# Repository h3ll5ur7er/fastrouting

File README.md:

# traxide

*trace* + *oxide*: a fast, dependency-free PCB autorouter for KiCad and every tool that speaks Specctra DSN: a modern alternative to Freerouting, written in Rust, using every CPU core and, when present, the GPU.

> traxide is young: it routes a 4-layer keyboard with an RP2350 completely in seconds, and KiCad 10's DRC finds the result clean, while Freerouting takes minutes and leaves violations. It reads KiCad's board files and Specctra DSN, and has met few boards yet. See the [benchmarks](docs/Benchmarks.md).

## Try it

Download traxide and its KiCad plugin from the repository's **Releases**: archives for Linux, Windows (x86-64 and ARM64 each) and macOS (universal), with nothing else to install, and a KiCad package for each. Between releases, every push builds the same in the **Binaries** workflow under the *Actions* tab. Or build it:

```bash
cargo build --release
# A KiCad 9 or 10 board, with the rules of its project: writes board.routed.kicad_pcb
target/release/traxide route board.kicad_pcb
# Or, as with Freerouting: in KiCad, File → Export → Specctra DSN, then
target/release/traxide route board.dsn        # writes board.ses, on all cores
target/release/traxide route --help           # profiles, threads, output
target/release/traxide route board.dsn --time-limit 60   # stop negotiating after a minute
target/release/traxide check board.dsn board.ses   # complete? rules broken?
# The same verdict as a DRC report in KiCad's JSON format (route takes --drc too)
target/release/traxide check board.dsn board.ses --drc board.drc.json
# In place of Freerouting: the same arguments, -drc report.json included
target/release/traxide freerouting -de board.dsn -do board.ses
# In KiCad: File → Import → Specctra Session
```

### From inside KiCad

traxide's KiCad plugin adds a **Route board** button to the PCB editor's toolbar (KiCad 9 and 10). It routes every unrouted connection of the open board and adds the routes as one step: *Edit → Undo traxide: route* takes them all back. The rules come from KiCad's net classes and the project's files. On a board with copper zones traxide then refills them around the routes, a step of its own, so taking the routes back takes two undos.

1. **Enable KiCad's API first**: *Preferences → Preferences… → Plugins → Enable KiCad API*. It is off by default, and **without it KiCad shows no traxide button at all**.
2. Download the KiCad package for your platform (`traxide-kicad-<version>-<platform>.zip`) from the Releases and install it with *Plugin and Content Manager → Install from File…*.
3. Restart the PCB editor: the button appears in its top toolbar. In KiCad 10, traxide's report (how much it routed, and what it could not) appears under the warning sign at the right end of the status bar; KiCad 9 shows the routes but not the report.

The package carries the traxide binary itself; there is no Python. From a terminal, `traxide route --kicad` does what the button does.

A copy of the binary named `freerouting` (`freerouting.exe` on Windows) takes Freerouting's arguments too, for tools that run Freerouting.

- **Wiki**: [`docs/Home.md`](docs/Home.md). Covers [research](docs/Research.md), [architecture](docs/Architecture.md) (iDesign, decomposed by volatility) and the [project plan](docs/Project-plan.md).
- **Tasks**: [`tasks/`](tasks), one Markdown file per task, grouped by milestone.

Both are plain files managed with [Genbeya](https://github.com/genbeya/genbeya). Open this folder in Genbeya to get the wiki and the board with live references.

## License

Licensed under either of

- Apache License, Version 2.0 ([LICENSE-APACHE](LICENSE-APACHE))
- MIT license ([LICENSE-MIT](LICENSE-MIT))

at your option.

Unless you explicitly state otherwise, any contribution intentionally submitted for inclusion in traxide by you, as defined in the Apache-2.0 license, shall be dual licensed as above, without any additional terms or conditions. traxide is written clean-room: see [Clean-room rules](docs/Development.md#clean-room-rules).

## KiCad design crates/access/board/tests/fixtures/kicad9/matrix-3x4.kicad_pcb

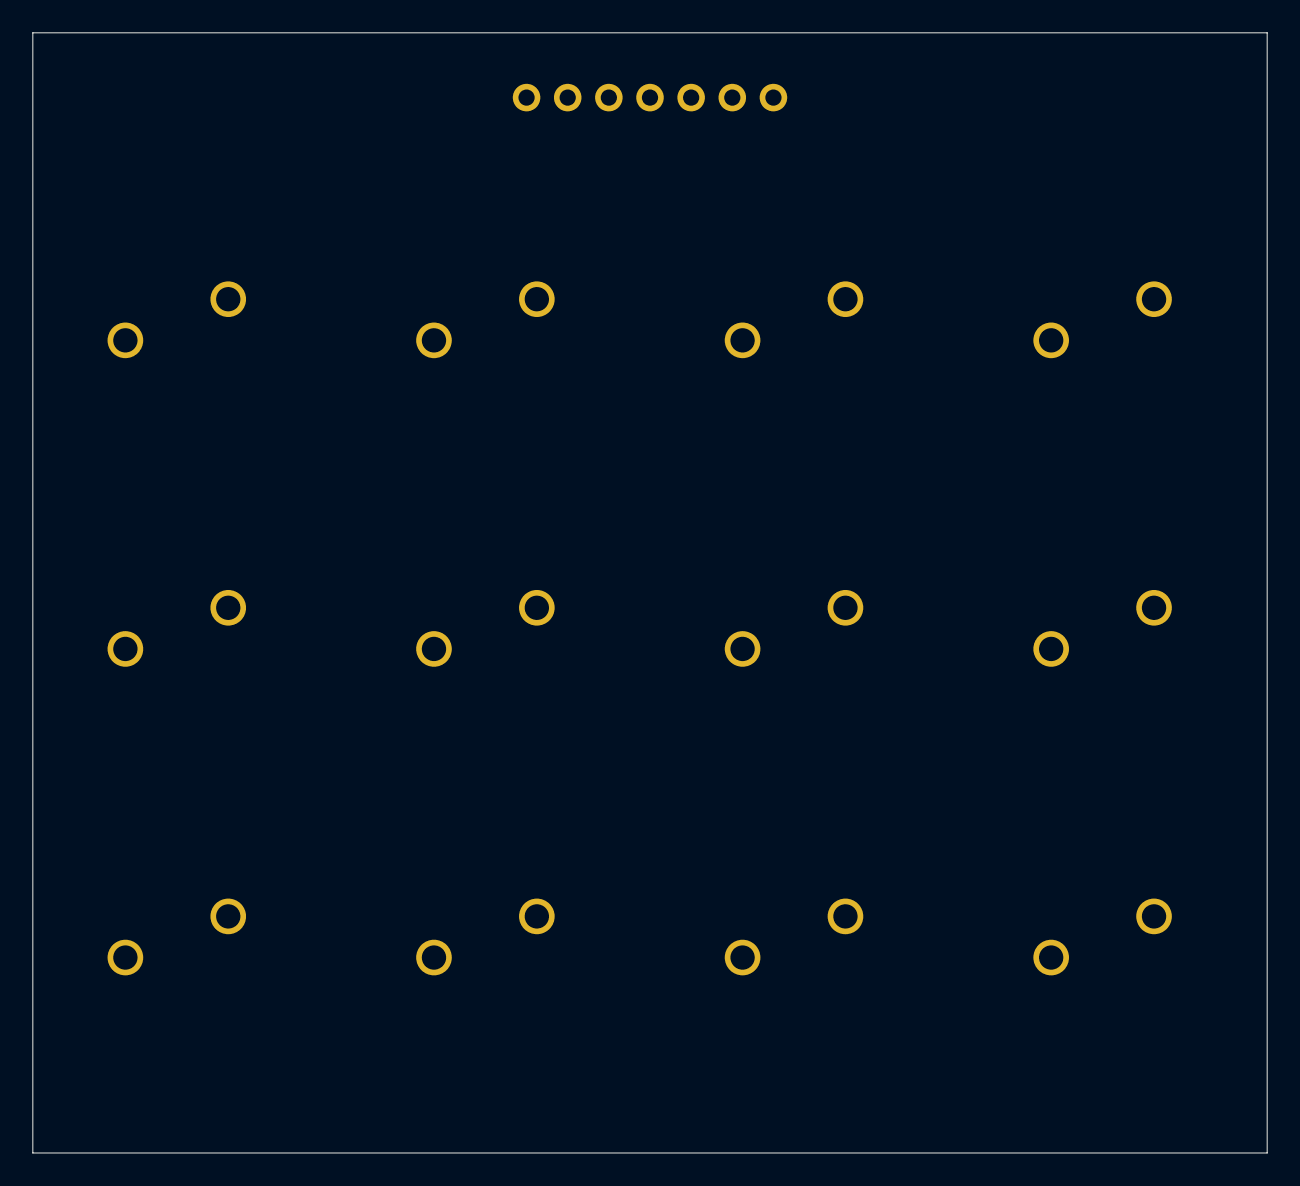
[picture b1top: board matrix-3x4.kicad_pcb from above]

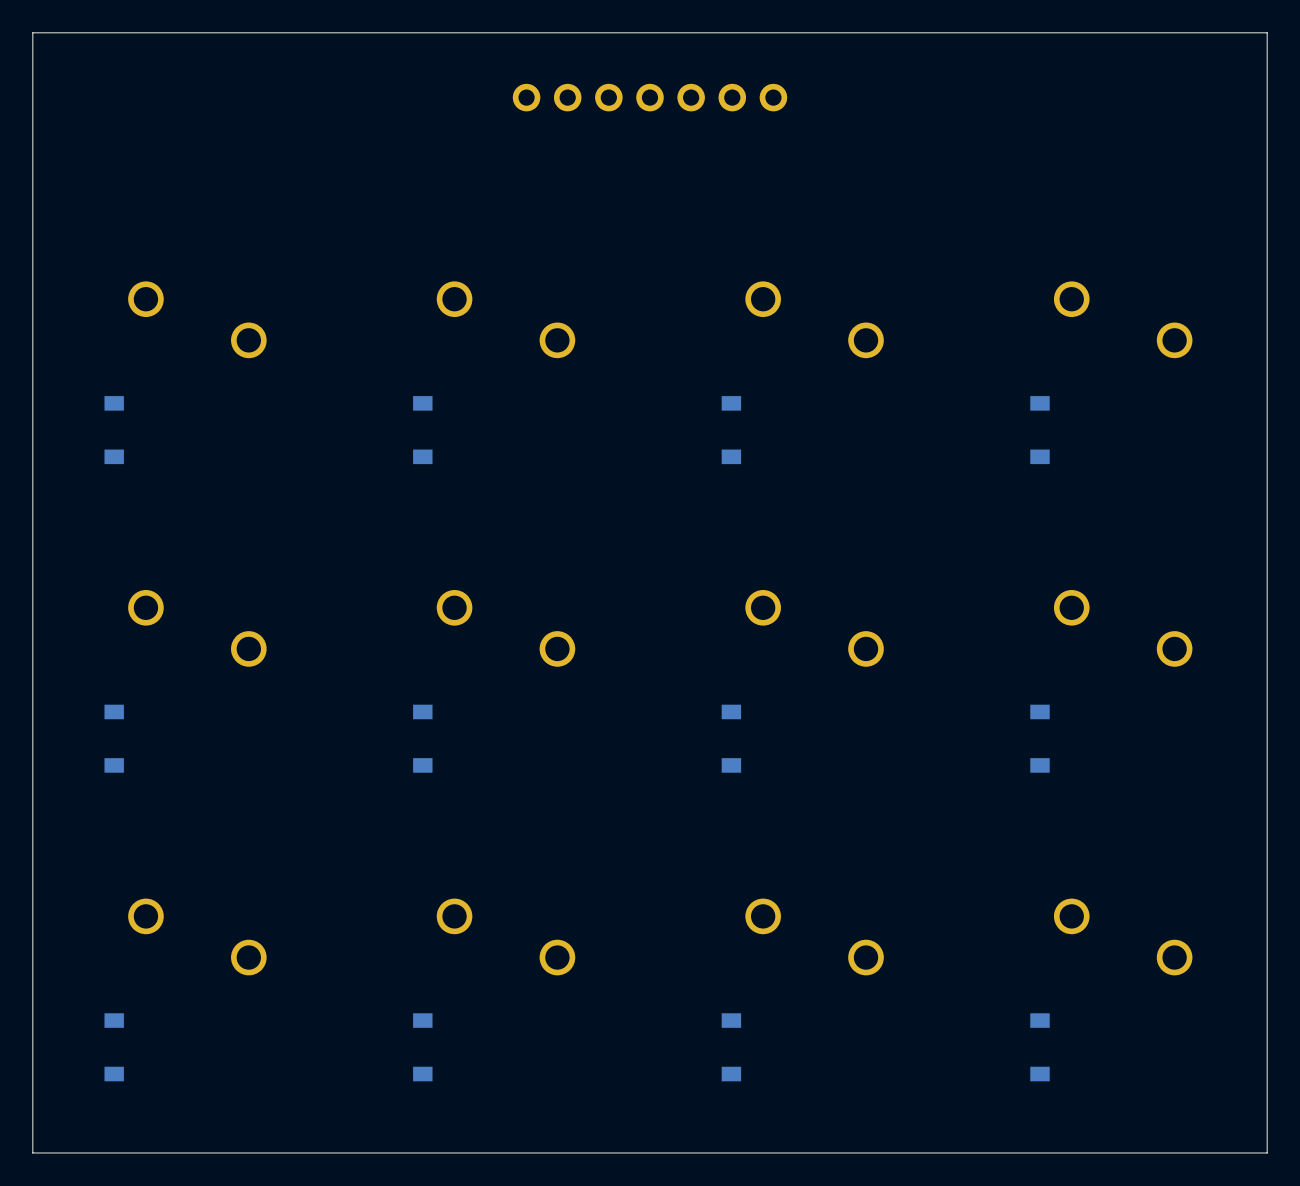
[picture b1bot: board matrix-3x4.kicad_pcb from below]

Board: 2 copper layers, 76.2 x 69.2 mm, 25 parts (12 on the bottom side), 19 nets, no tracks yet.

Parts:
D1, D2, D3, D4, D5, D6, D7, D8, D9, D10, D11, D12: D
J1: J
SW1, SW2, SW3, SW4, SW5, SW6, SW7, SW8, SW9, SW10, SW11, SW12: SW

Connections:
COL0: J1.4, SW1.1, SW5.1, SW9.1
COL1: J1.5, SW2.1, SW6.1, SW10.1
COL2: J1.6, SW3.1, SW7.1, SW11.1
COL3: J1.7, SW4.1, SW8.1, SW12.1
K0_0: D1.2, SW1.2
K0_1: D2.2, SW2.2
K0_2: D3.2, SW3.2
K0_3: D4.2, SW4.2
K1_0: D5.2, SW5.2
K1_1: D6.2, SW6.2
K1_2: D7.2, SW7.2
K1_3: D8.2, SW8.2
K2_0: D9.2, SW9.2
K2_1: D10.2, SW10.2
K2_2: D11.2, SW11.2
K2_3: D12.2, SW12.2
ROW0: D1.1, D2.1, D3.1, D4.1, J1.1
ROW1: D5.1, D6.1, D7.1, D8.1, J1.2
ROW2: D9.1, D10.1, D11.1, D12.1, J1.3

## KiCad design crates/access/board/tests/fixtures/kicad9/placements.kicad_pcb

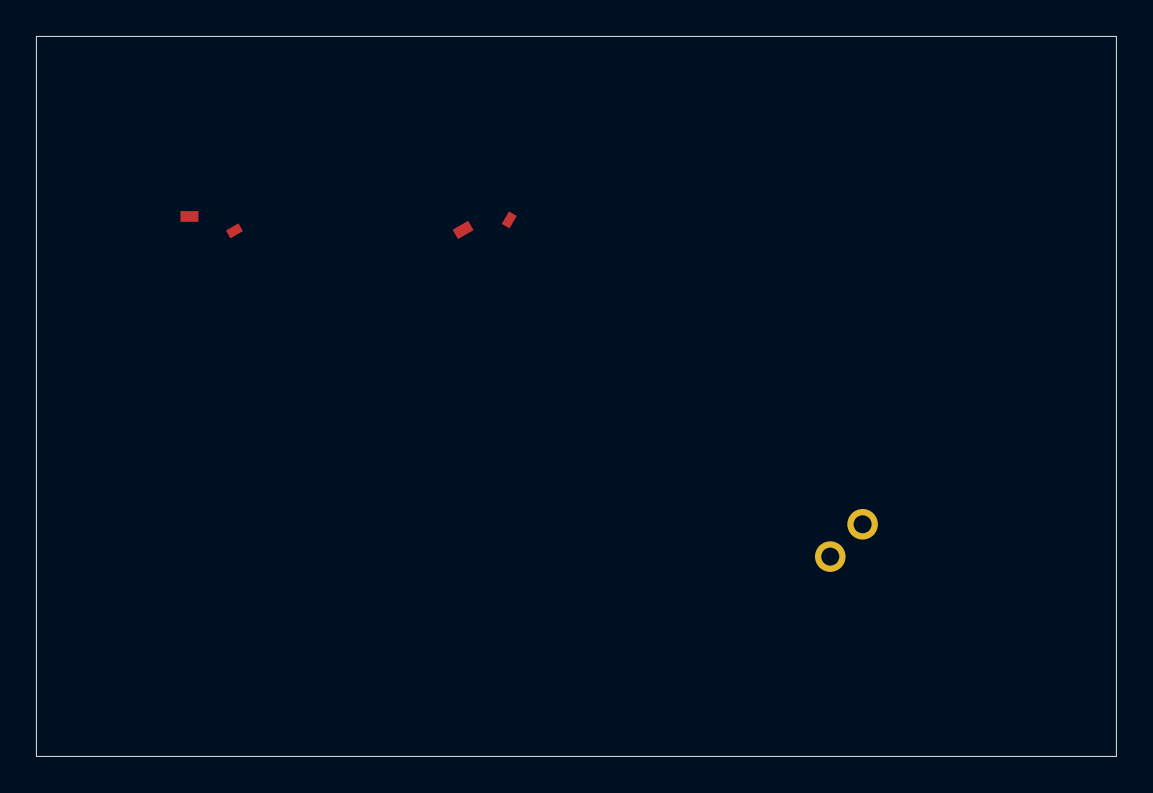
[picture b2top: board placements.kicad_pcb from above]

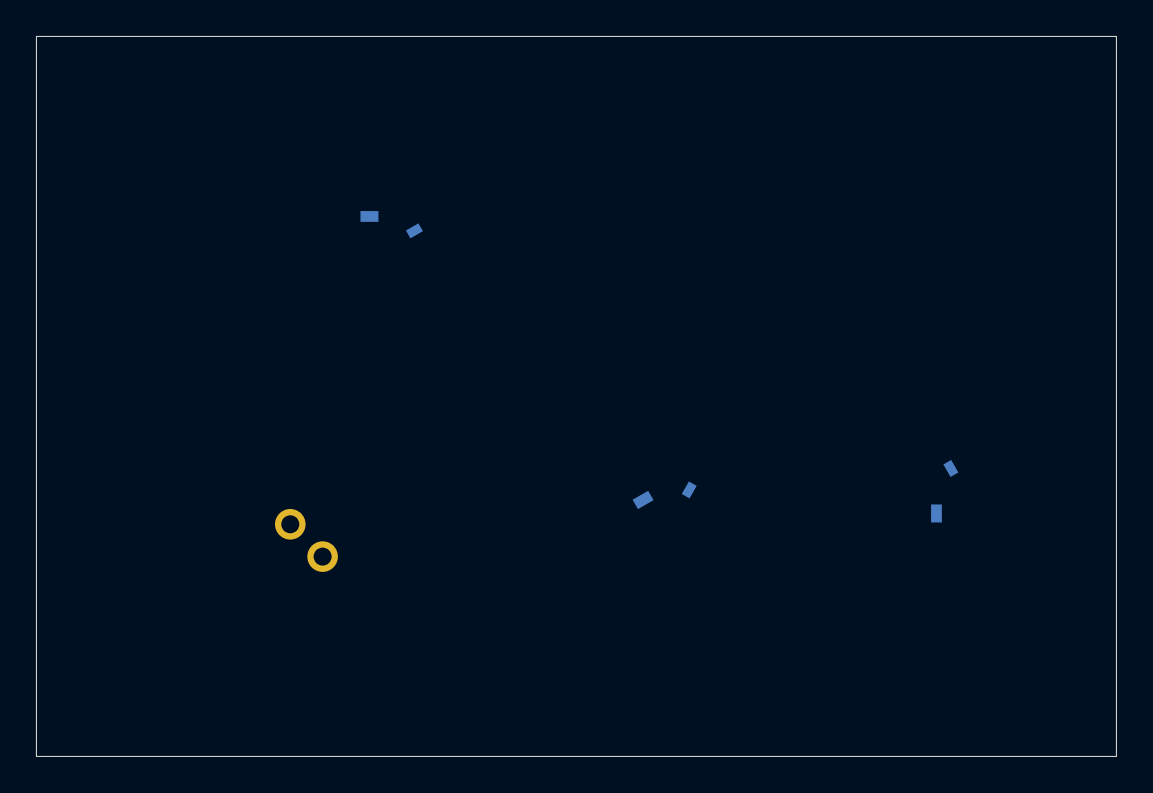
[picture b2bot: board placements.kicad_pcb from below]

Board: 2 copper layers, 60.0 x 40.0 mm, 6 parts (3 on the bottom side), 5 nets, no tracks yet.

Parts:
J1: J
U1, U2, U3, U4, U5: U

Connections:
A: J1.1, U1.1, U1.2
B: J1.2, U2.1, U2.2
C: U3.1, U3.2
D: U4.1, U4.2
E: U5.1, U5.2

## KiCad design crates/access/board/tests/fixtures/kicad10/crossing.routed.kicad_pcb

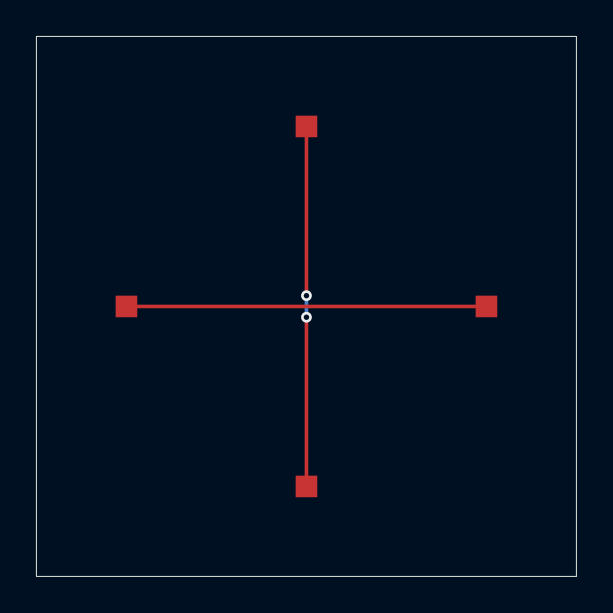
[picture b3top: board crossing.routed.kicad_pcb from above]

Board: 2 copper layers, 30.0 x 30.0 mm, 4 parts (0 on the bottom side), 2 nets.

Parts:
TP1, TP2, TP3, TP4: TP

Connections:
ACROSS: TP1.1, TP2.1
DOWN: TP3.1, TP4.1

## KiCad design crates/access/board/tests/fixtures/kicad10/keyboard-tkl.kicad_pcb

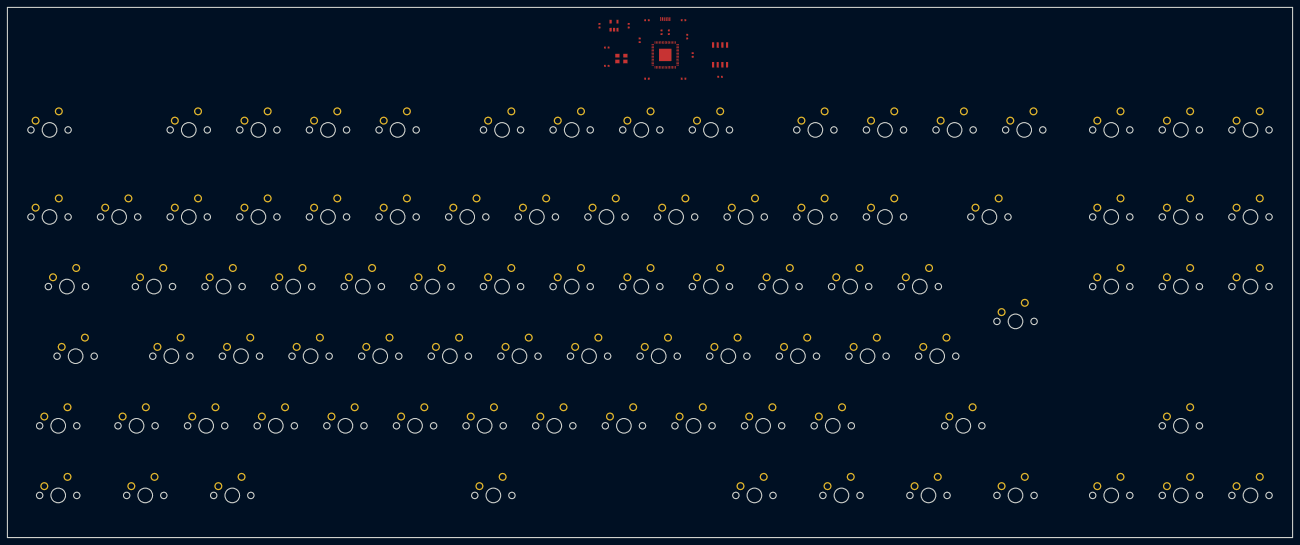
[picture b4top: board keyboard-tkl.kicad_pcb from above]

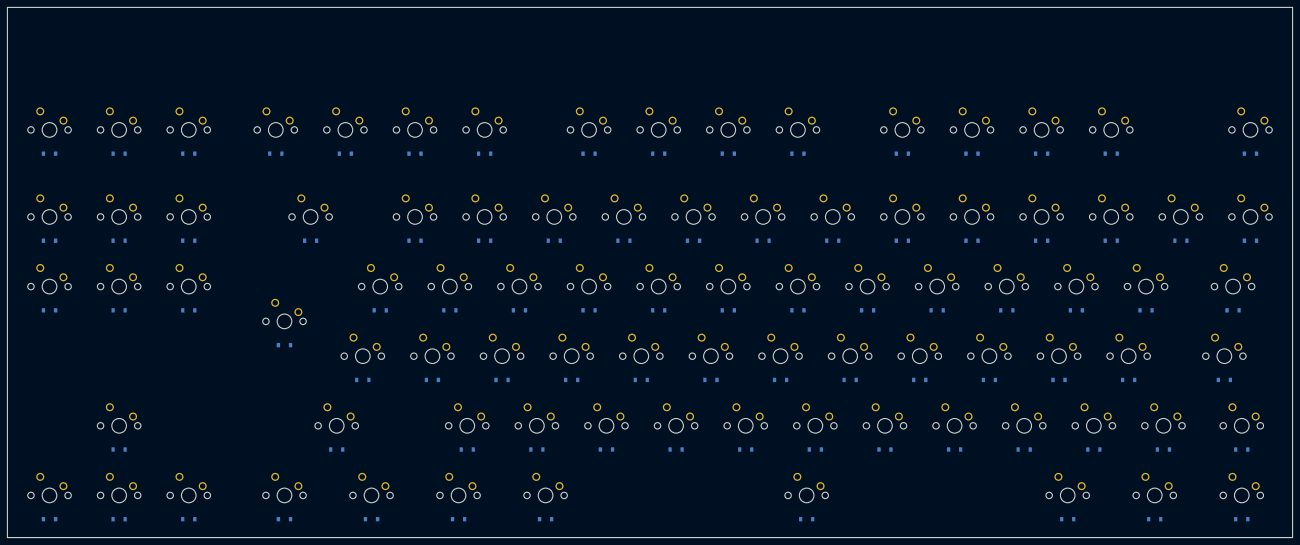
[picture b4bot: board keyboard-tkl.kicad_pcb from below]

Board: 4 copper layers, 351.7 x 145.1 mm, 195 parts (88 on the bottom side), 129 nets, no tracks yet.

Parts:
C1, C2, C3, C4, C5, C6, C7, C8, C9, C10: C
D1, D2, D3, D4, D5, D6, D7, D8, D9, D10, D11, D12, D13, D14, D15, D16, D17, D18, D19, D20, D21, D22, D23, D24, D25, D26, D27, D28, D29, D30, D31, D32, D33, D34, D35, D36, D37, D38, D39, D40, D41, D42, D43, D44, D45, D46, D47, D48, D49, D50, D51, D52, D53, D54, D55, D56, D57, D58, D59, D60, D61, D62, D63, D64, D65, D66, D67, D68, D69, D70, D71, D72, D73, D74, D75, D76, D77, D78, D79, D80, D81, D82, D83, D84, D85, D86, D87, D88: D
J1: J
R1, R2, R3, R4: R
SW1, SW2, SW3, SW4, SW5, SW6, SW7, SW8, SW9, SW10, SW11, SW12, SW13, SW14, SW15, SW16, SW17, SW18, SW19, SW20, SW21, SW22, SW23, SW24, SW25, SW26, SW27, SW28, SW29, SW30, SW31, SW32, SW33, SW34, SW35, SW36, SW37, SW38, SW39, SW40, SW41, SW42, SW43, SW44, SW45, SW46, SW47, SW48, SW49, SW50, SW51, SW52, SW53, SW54, SW55, SW56, SW57, SW58, SW59, SW60, SW61, SW62, SW63, SW64, SW65, SW66, SW67, SW68, SW69, SW70, SW71, SW72, SW73, SW74, SW75, SW76, SW77, SW78, SW79, SW80, SW81, SW82, SW83, SW84, SW85, SW86, SW87, SW88: SW
U1, U2, U3: U
Y1: Y

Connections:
1V1: C9.1, C10.1, U1.5, U1.40
3V3: C2.1, C5.1, C6.1, C7.1, C8.1, U1.1, U1.2, U1.14, U1.38, U1.44, U1.50, U2.8, U3.5
CC1: J1.2, R3.1
CC2: J1.5, R4.1
COL0: SW1.1, SW17.1, SW34.1, SW51.1, SW64.1, SW78.1, U1.22
COL1: SW2.1, SW18.1, SW35.1, SW52.1, SW65.1, SW79.1, U1.23
COL2: SW3.1, SW19.1, SW36.1, SW53.1, SW66.1, SW80.1, U1.24
COL3: SW4.1, SW20.1, SW37.1, SW54.1, SW67.1, SW81.1, U1.25
COL4: SW5.1, SW21.1, SW38.1, SW55.1, SW68.1, SW82.1, U1.26
COL5: SW6.1, SW22.1, SW39.1, SW56.1, SW69.1, SW83.1, U1.27
COL6: SW7.1, SW23.1, SW40.1, SW57.1, SW70.1, SW84.1, U1.28
COL7: SW8.1, SW24.1, SW41.1, SW58.1, SW71.1, SW85.1, U1.29
COL8: SW9.1, SW25.1, SW42.1, SW59.1, SW72.1, SW86.1, U1.30
COL9: SW10.1, SW26.1, SW43.1, SW60.1, SW73.1, SW87.1, U1.6
COL10: SW11.1, SW27.1, SW44.1, SW61.1, SW74.1, SW88.1, U1.7
COL11: SW12.1, SW28.1, SW45.1, SW62.1, SW75.1, U1.8
COL12: SW13.1, SW29.1, SW46.1, SW63.1, SW76.1, U1.9
COL13: SW14.1, SW30.1, SW47.1, SW77.1, U1.10
COL14: SW15.1, SW31.1, SW48.1, U1.11
COL15: SW16.1, SW32.1, SW49.1, U1.12
COL16: SW33.1, SW50.1, U1.13
GND: C1.2, C2.2, C3.2, C4.2, C5.2, C6.2, C7.2, C8.2, C9.2, C10.2, J1.1, R3.2, R4.2, U1.61, U2.4, U3.2, Y1.2, Y1.4
K0_0: D1.2, SW1.2
K0_1: D2.2, SW2.2
K0_2: D3.2, SW3.2
K0_3: D4.2, SW4.2
K0_4: D5.2, SW5.2
K0_5: D6.2, SW6.2
K0_6: D7.2, SW7.2
K0_7: D8.2, SW8.2
K0_8: D9.2, SW9.2
K0_9: D10.2, SW10.2
K0_10: D11.2, SW11.2
K0_11: D12.2, SW12.2
K0_12: D13.2, SW13.2
K0_13: D14.2, SW14.2
K0_14: D15.2, SW15.2
K0_15: D16.2, SW16.2
K1_0: D17.2, SW17.2
K1_1: D18.2, SW18.2
K1_2: D19.2, SW19.2
K1_3: D20.2, SW20.2
K1_4: D21.2, SW21.2
K1_5: D22.2, SW22.2
K1_6: D23.2, SW23.2
K1_7: D24.2, SW24.2
K1_8: D25.2, SW25.2
K1_9: D26.2, SW26.2
K1_10: D27.2, SW27.2
K1_11: D28.2, SW28.2
K1_12: D29.2, SW29.2
K1_13: D30.2, SW30.2
K1_14: D31.2, SW31.2
K1_15: D32.2, SW32.2
K1_16: D33.2, SW33.2
K2_0: D34.2, SW34.2
K2_1: D35.2, SW35.2
K2_2: D36.2, SW36.2
K2_3: D37.2, SW37.2
K2_4: D38.2, SW38.2
K2_5: D39.2, SW39.2
K2_6: D40.2, SW40.2
K2_7: D41.2, SW41.2
K2_8: D42.2, SW42.2
K2_9: D43.2, SW43.2
K2_10: D44.2, SW44.2
K2_11: D45.2, SW45.2
K2_12: D46.2, SW46.2
K2_13: D47.2, SW47.2
K2_14: D48.2, SW48.2
K2_15: D49.2, SW49.2
K2_16: D50.2, SW50.2
K3_0: D51.2, SW51.2
K3_1: D52.2, SW52.2
K3_2: D53.2, SW53.2
K3_3: D54.2, SW54.2
K3_4: D55.2, SW55.2
K3_5: D56.2, SW56.2
K3_6: D57.2, SW57.2
K3_7: D58.2, SW58.2
K3_8: D59.2, SW59.2
K3_9: D60.2, SW60.2
K3_10: D61.2, SW61.2
K3_11: D62.2, SW62.2
K3_12: D63.2, SW63.2
K4_0: D64.2, SW64.2
K4_1: D65.2, SW65.2
K4_2: D66.2, SW66.2
K4_3: D67.2, SW67.2
K4_4: D68.2, SW68.2
K4_5: D69.2, SW69.2
K4_6: D70.2, SW70.2
K4_7: D71.2, SW71.2
K4_8: D72.2, SW72.2
K4_9: D73.2, SW73.2
K4_10: D74.2, SW74.2
K4_11: D75.2, SW75.2
K4_12: D76.2, SW76.2
K4_13: D77.2, SW77.2
K5_0: D78.2, SW78.2
K5_1: D79.2, SW79.2
K5_2: D80.2, SW80.2
K5_3: D81.2, SW81.2
K5_4: D82.2, SW82.2
K5_5: D83.2, SW83.2
K5_6: D84.2, SW84.2
K5_7: D85.2, SW85.2
K5_8: D86.2, SW86.2
K5_9: D87.2, SW87.2
K5_10: D88.2, SW88.2
QSPI_SCLK: U1.35, U2.6
QSPI_SD0: U1.34, U2.5
QSPI_SD1: U1.32, U2.2
QSPI_SD2: U1.33, U2.3
QSPI_SD3: U1.36, U2.7
QSPI_SS: U1.31, U2.1
ROW0: D1.1, D2.1, D3.1, D4.1, D5.1, D6.1, D7.1, D8.1, D9.1, D10.1, D11.1, D12.1, D13.1, D14.1, D15.1, D16.1, U1.16
ROW1: D17.1, D18.1, D19.1, D20.1, D21.1, D22.1, D23.1, D24.1, D25.1, D26.1, D27.1, D28.1, D29.1, D30.1, D31.1, D32.1, D33.1, U1.17
ROW2: D34.1, D35.1, D36.1, D37.1, D38.1, D39.1, D40.1, D41.1, D42.1, D43.1, D44.1, D45.1, D46.1, D47.1, D48.1, D49.1, D50.1, U1.18
ROW3: D51.1, D52.1, D53.1, D54.1, D55.1, D56.1, D57.1, D58.1, D59.1, D60.1, D61.1, D62.1, D63.1, U1.19
ROW4: D64.1, D65.1, D66.1, D67.1, D68.1, D69.1, D70.1, D71.1, D72.1, D73.1, D74.1, D75.1, D76.1, D77.1, U1.20
ROW5: D78.1, D79.1, D80.1, D81.1, D82.1, D83.1, D84.1, D85.1, D86.1, D87.1, D88.1, U1.21
USB_DM: R2.2, U1.53
USB_DM_C: J1.4, R2.1
USB_DP: R1.2, U1.52
USB_DP_C: J1.3, R1.1
VBUS: C1.1, J1.6, U3.1, U3.3
XIN: C3.1, U1.3, Y1.1
XOUT: C4.1, U1.4, Y1.3

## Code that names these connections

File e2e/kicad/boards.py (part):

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            ], back=True)
    pins = {16 + i: f"ROW{i}" for i in range(6)} | {22 + i: f"COL{i}" for i in range(9)}
    pins |= {6 + i: f"COL{9 + i}" for i in range(8)}
    pins |= {1: "3V3", 2: "3V3", 3: "XIN", 4: "XOUT", 5: "1V1", 14: "3V3"}
    pins |= {31: "QSPI_SS", 32: "QSPI_SD1", 33: "QSPI_SD2", 34: "QSPI_SD0", 35: "QSPI_SCLK", 36: "QSPI_SD3",
             38: "3V3", 40: "1V1", 44: "3V3"}
    pins |= {52: "USB_DP", 53: "USB_DM", 50: "3V3"}
    mcu_x, mcu_y = 180.0, 13.0
    builder.footprint("U1", mcu_x, mcu_y, qfn60(pins))
    builder.footprint("J1", mcu_x, 3.2, [
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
